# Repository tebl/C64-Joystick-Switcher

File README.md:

# C64 Joystick Switcher
I was watching [MsMadLemon](https://www.youtube.com/channel/UCSlMemxuBOFu6Rz_Al02nHQ) on [Youtube](https://youtu.be/DOF_CZoSF5g) the other day and she was making an autofire circuit, so naturally I wanted to build one too! Starting with the [C64 Mega Switcher](https://github.com/tebl/C64-Mega-Switcher) for the Commodore 64 (when you want to use Sega Genesis or Mega Drive Controllers instead), I stripped away some parts to clear space for the autofire parts, redesigned it a couple of times and then finally sketched out the whole thing again in order to figure out all the ways it didn't work. The last one thankfully worked, so now it's open and available for anyone with fingers they are willing to risk burning with a soldering iron (don't do that by the way, it hurts)!

## Building the switcher
Soldering together the few components should be easy going as long as you have access to reasonable tools, personally I'm using a cheap soldering station with adjustable temperature so no need to go expensive if you don't have to. Use 60/40 soldering tin of reasonable quality, but stay away from the lead-free stuff unless you have experience working with it.

Start by studying the PCB, both sides and perform dry fits to see that you have an idea of where everything goes since removing things is always a lot harder than getting it right in the first place (match orientation to symbols, see gallery images for reference if you're unsure). The diodes are installed standing, the stripe goes into the board so that it is laying directly against the board - a hint for making these look pretty, is wrapping one of the wires around a small screwdriver to get the loops looking almost identical!

The female DB9 connectors used for port 1/2 comes with a metal shroud, this comes off when you remove the two screws that would be in the way anyway (see image above for reference). Given that the C64 ports are made out of plastic, the metal shroud is not needed though you could possibly keep it by gluing it to the connector if you really wanted to, alternatively you could also fill the mounting holes with solder to keep them together afterwards. Do a testfit of the connectors with the C64 before soldering them to the board, this is recommended in order to avoid adding any stress to the C64 board.

Other than that, just take your time when doing the assembly - start by installing the smallest components first and then work your way up from there. Before actually plugging in anything into any antique computers, do a thorough visual inspection for any accidental solder-bridges. As a finishing note, I recommend putting something under the PCB to help support when pushing the buttons.

## Using the switcher
Firmly insert the switcher into the C64, making sure that it is inserted the whole way and fits firmly without feeling loose. When playing a game, if you encounter a game that expects a joystick inserted into the other port you can use the switches to change the currently active port.

**WARNING!**
 - Do **NOT** move any of the jumpers while the computer is switched on, doing so may cause damage to it. Always power off first!
 - Do **NOT** jumper so that more than one button/direction does the same thing, for example: if you jumper the B1 button for UP, then you have to REMOVE the jumper enabling D-PAD UP!
 - Do **NOT** use with actual Sega Genesis or Mega Drive controllers, if you want to use one of those - use [C64 Mega Switcher](https://github.com/tebl/C64-Mega-Switcher) instead.

You can use any common Atari-style joystick such as the Competition Pro and Zipstick, they are the ones I've tested with and currently also have in my collection. You can use the secondary fire button if you have one wired with this capability, most commonly the pinout is compatible with the Sega Master System gamepad. An auto-fire circuit has been added to the module, this can be handy if your controller does not include this functionality. 

# Schematic
The supplied KiCad files should be sufficient as both a schematic and as a  starting point for ordering PCBs (basically you could just zip the contents of the export folder and upload that on a fabrication site), the schematic is also available in [PDF-format](https://github.com/tebl/C64-Joystick-Switcher/raw/master/export/C64%20Joystick%20Switcher.pdf) and this is what you'll need to print and work your way through this things don't work as expected after assembly.

# BOM
Most parts should be easy to get a hold of from your favourite local electronic component shop, but given that I don't have access to such shops where I live so everything was based on whatever I could get cheapest from ebay/AliExpress (free shipping most places, but plan on waiting 3-4 weeks though). Pin headers are bought as strips with 40 pins, single or double rows, that you break into the specified sizes. Any amounts given in paranthesis are for optional functionality, mainly autofire and capability to utilize the secondary fire button if you have one. 

| Reference    | Item                                  | Count |
| ------------ | ------------------------------------- | ----- |
| PCB          | Fabricate using Gerber files ([order](https://www.pcbway.com/project/shareproject/Commodore_64_Joystick_Switcher__Revision_C_.html?inviteid=88707))          |     1 |
| C1-C4        | 100nF capacitor                       |     4 |
| C5           | 10uF electrolytic capacitor           |    (1)|
| D1,D2        | 5mm LED                               |     2 |
| J1,J2        | Female DB9 right-angle connector      |     2 |
| J3           | Male DB9 right-angle connector        |     1 |
| J4,J5        | 2x3-pin straight header               |     2 |
| JP2          | 3-pin straight header                 |     1 |
| Q1           | BC547 transistor (TO-92)              |    (1)|
| R1,R2        | 10k ohm resistor                      |     2 | 
| R3,R4        | 220 ohm resistor                      |     2 |
| R5,R7        | 2k2 (2200) ohm resistor               |    (2)|
| R6           | 100k ohm resistor                     |    (1)|
| R9           | 10k ohm resistor                      |    (1)| 
| RV1          | 10k ohm potentiometer (RM-065)        |    (1)| 
| U1,U2        | 74HCT4053 or CD4053 (DIP-16)          |     2 |
| U3           | NE555 (DIP-8)                         |     1 |
| U4           | NE555 (DIP-8)                         |    (1)|
| SW1,SW2      | SPST momentary push button            |     2 |

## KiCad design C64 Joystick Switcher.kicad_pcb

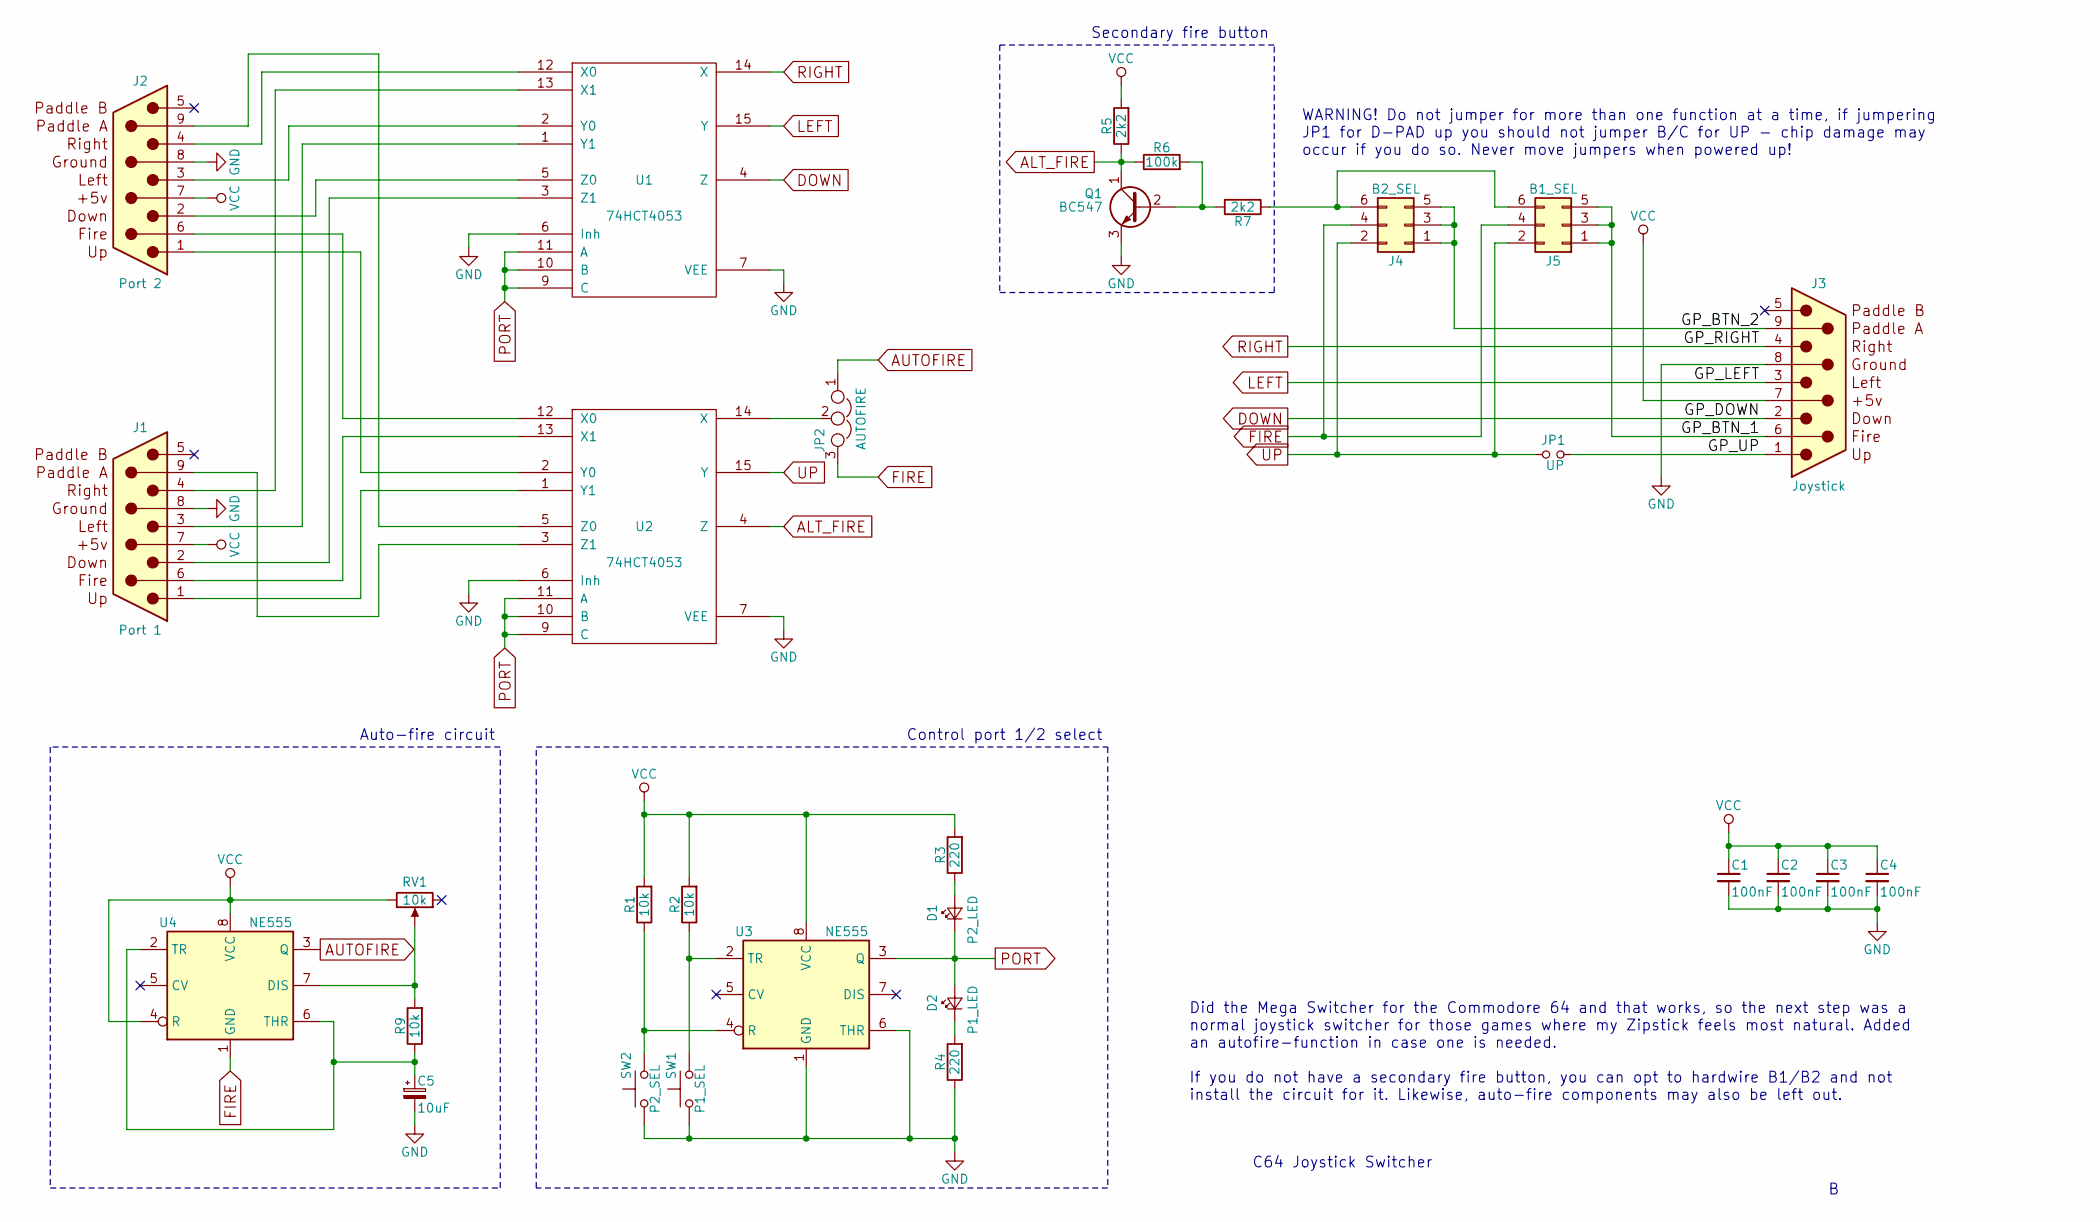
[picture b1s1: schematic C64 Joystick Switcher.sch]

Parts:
C1, C2, C3, C4: 100nF; C_Disc_D4.7mm_W2.5mm_P5.00mm
C5: 10uF; CP_Radial_D5.0mm_P2.50mm
D1: P2_LED; LED_D5.0mm
D2: P1_LED; LED_D5.0mm
J1: Port 1; DSUB-9_Female_Horizontal_P2.77x2.84mm_EdgePinOffset7.70mm_H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
J2: Port 2; DSUB-9_Female_Horizontal_P2.77x2.84mm_EdgePinOffset7.70mm_H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
J3: Joystick; DSUB-9_Male_Horizontal_P2.77x2.84mm_EdgePinOffset7.70mm_Hou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
J4: B2_SEL; Pin_Header_Straight_2x03_Pitch2.54mm
J5: B1_SEL; Pin_Header_Straight_2x03_Pitch2.54mm
JP1: UP; Pin_Header_Straight_1x02_Pitch2.54mm
JP2: AUTOFIRE; Pin_Header_Straight_1x03_Pitch2.54mm
Q1: BC547; TO-92_Inline_Wide
R1, R2, R9: 10k; R_Axial_DIN0207_L6.3mm_D2.5mm_P10.16mm_Horizontal
R3, R4: 220; R_Axial_DIN0207_L6.3mm_D2.5mm_P10.16mm_Horizontal
R5, R7: 2k2; R_Axial_DIN0207_L6.3mm_D2.5mm_P10.16mm_Horizontal
R6: 100k; R_Axial_DIN0207_L6.3mm_D2.5mm_P10.16mm_Horizontal
RV1: 10k; Potentiometer_Triwood_RM-065
SW1: P1_SEL; SW_PUSH_6mm
SW2: P2_SEL; SW_PUSH_6mm
U1, U2: 74HCT4053; DIP-16_W7.62mm_Socket
U3, U4: NE555; DIP-8_W7.62mm_Socket

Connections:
/GP_BTN_1: J3.6, J5.1, J5.3, J5.5
/GP_BTN_2: J3.9, J4.1, J4.3, J4.5
/GP_UP: J3.1, JP1.2
ALT_FIRE: Q1.1 (C), R5.1, R6.1, U2.4 (Z)
AUTOFIRE: JP2.1, U4.3 (Q)
DOWN: J3.2, U1.4 (Z)
FIRE: J4.4, J5.4, JP2.3, U4.1 (GND)
GND: C1.2, C2.2, C3.2, C4.2, C5.2, J1.8 (GND), J2.8 (GND), J3.8 (GND), Q1.3 (E), R4.1, SW1.1, SW2.1, U1.6 (Inh), U1.7 (VEE), U1.8 (GND), U2.6 (Inh), U2.7 (VEE), U2.8 (GND), U3.1 (GND), U3.6 (THR)
LEFT: J3.3, U1.15 (Y)
unnamed: C5.1, R9.1, U4.2 (TR), U4.6 (THR)
unnamed: D1.2 (A), R3.1
unnamed: D2.1 (K), R4.2
unnamed: J1.1, U2.1 (Y1)
unnamed: J1.2, U1.3 (Z1)
unnamed: J1.3, U1.1 (Y1)
unnamed: J1.4, U1.13 (X1)
unnamed: J1.6, U2.13 (X1)
unnamed: J1.9, U2.3 (Z1)
unnamed: J2.1, U2.2 (Y0)
unnamed: J2.2, U1.5 (Z0)
unnamed: J2.3, U1.2 (Y0)
unnamed: J2.4, U1.12 (X0)
unnamed: J2.6, U2.12 (X0)
unnamed: J2.9, U2.5 (Z0)
unnamed: J4.6, J5.6, R7.1
unnamed: JP2.2, U2.14 (X)
unnamed: Q1.2 (B), R6.2, R7.2
unnamed: R1.1, SW2.2, U3.4 (R)
unnamed: R2.1, SW1.2, U3.2 (TR)
unnamed: R9.2, RV1.2, U4.7 (DIS)
PORT: D1.1 (K), D2.2 (A), U1.9 (C), U1.10 (B), U1.11 (A), U2.9 (C), U2.10 (B), U2.11 (A), U3.3 (Q)
RIGHT: J3.4, U1.14 (X)
UP: J4.2, J5.2, JP1.1, U2.15 (Y)
VCC: C1.1, C2.1, C3.1, C4.1, J1.7 (VCC), J2.7 (VCC), J3.7 (VCC), R1.2, R2.2, R3.2, R5.2, RV1.3, U1.16 (VCC), U2.16 (VCC), U3.8 (VCC), U4.4 (R), U4.8 (VCC)

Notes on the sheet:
C64 Joystick Switcher
WARNING! Do not jumper for more than one function at a time, if jumpering JP1 for D-PAD up you should not jumper B/C for UP - chip damage may occur if you do so. Never move jumpers when powered up!
Did the Mega Switcher for the Commodore 64 and that works, so the next step was a normal joystick switcher for those games where my Zipstick feels most natural. Added an autofire-function in case one is needed. If you do not have a secondary fire button, you can opt to hardwire B1/B2 and not instal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
Auto-fire circuit
Control port 1/2 select
Secondary fire button

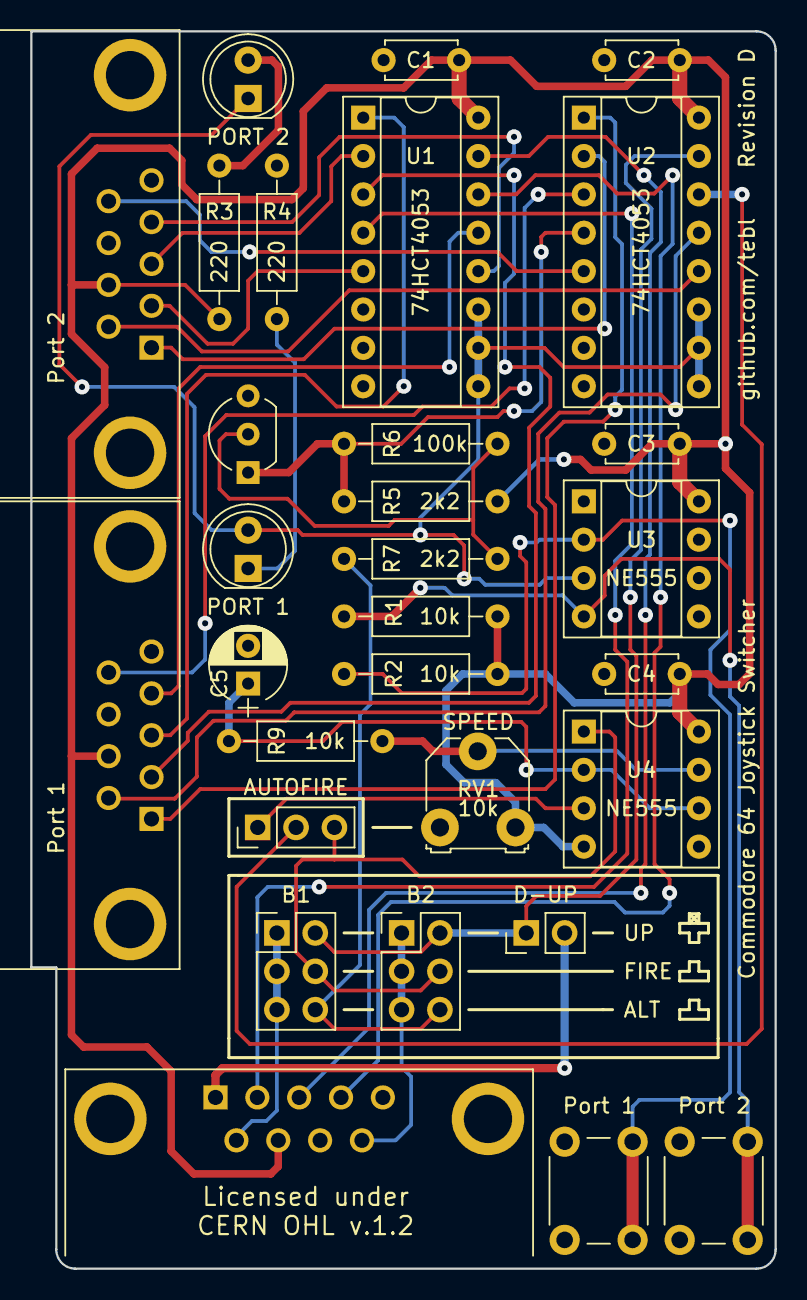
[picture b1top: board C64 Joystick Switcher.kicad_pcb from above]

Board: 2 copper layers, 49.3 x 81.9 mm, 30 parts (0 on the bottom side), 34 nets.

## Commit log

2019-09-26 Drafted up first layout
2019-10-20 Gerber export
2019-12-25 Replace auto-fire circuit
2020-01-25 Auto-fire should now work
2020-01-25 Updated description
2020-03-10 Added pictures
2020-03-10 Fix image
2020-03-10 Added image
2020-03-10 Update pcbway url
2021-11-22 .gitignore updated to exclude fp-info-cache and other files
2021-11-24 Simplified routing and reduced number of vias by more than 55%
2021-11-25 Deleted some gerber-files that does not contain pcb-relevant data
2021-11-26 Small layout improvements
2021-11-27 More small layout improvements
2023-02-25 Add TODO

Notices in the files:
C64 Joystick Switcher.kicad_pcb:
Licensed under
CERN OHL v.1.2
